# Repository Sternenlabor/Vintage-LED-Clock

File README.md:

# Vintage-LED-Clock
# WiFi configuration
SSID and credentials are kept in a separate file which is not included in GIT repository.   
Create file *credentials.h* in *src* folder and add SSID and WiFi password.   
e.g.:

    #ifndef _CREDENTIALS_H_
    #define _CREDENTIALS_H_

    const char cstrSSID[] = "MyNetwork";
    const char cstrPWD[] = "secret";

    #endif /* _CREDENTIALS_H_ */

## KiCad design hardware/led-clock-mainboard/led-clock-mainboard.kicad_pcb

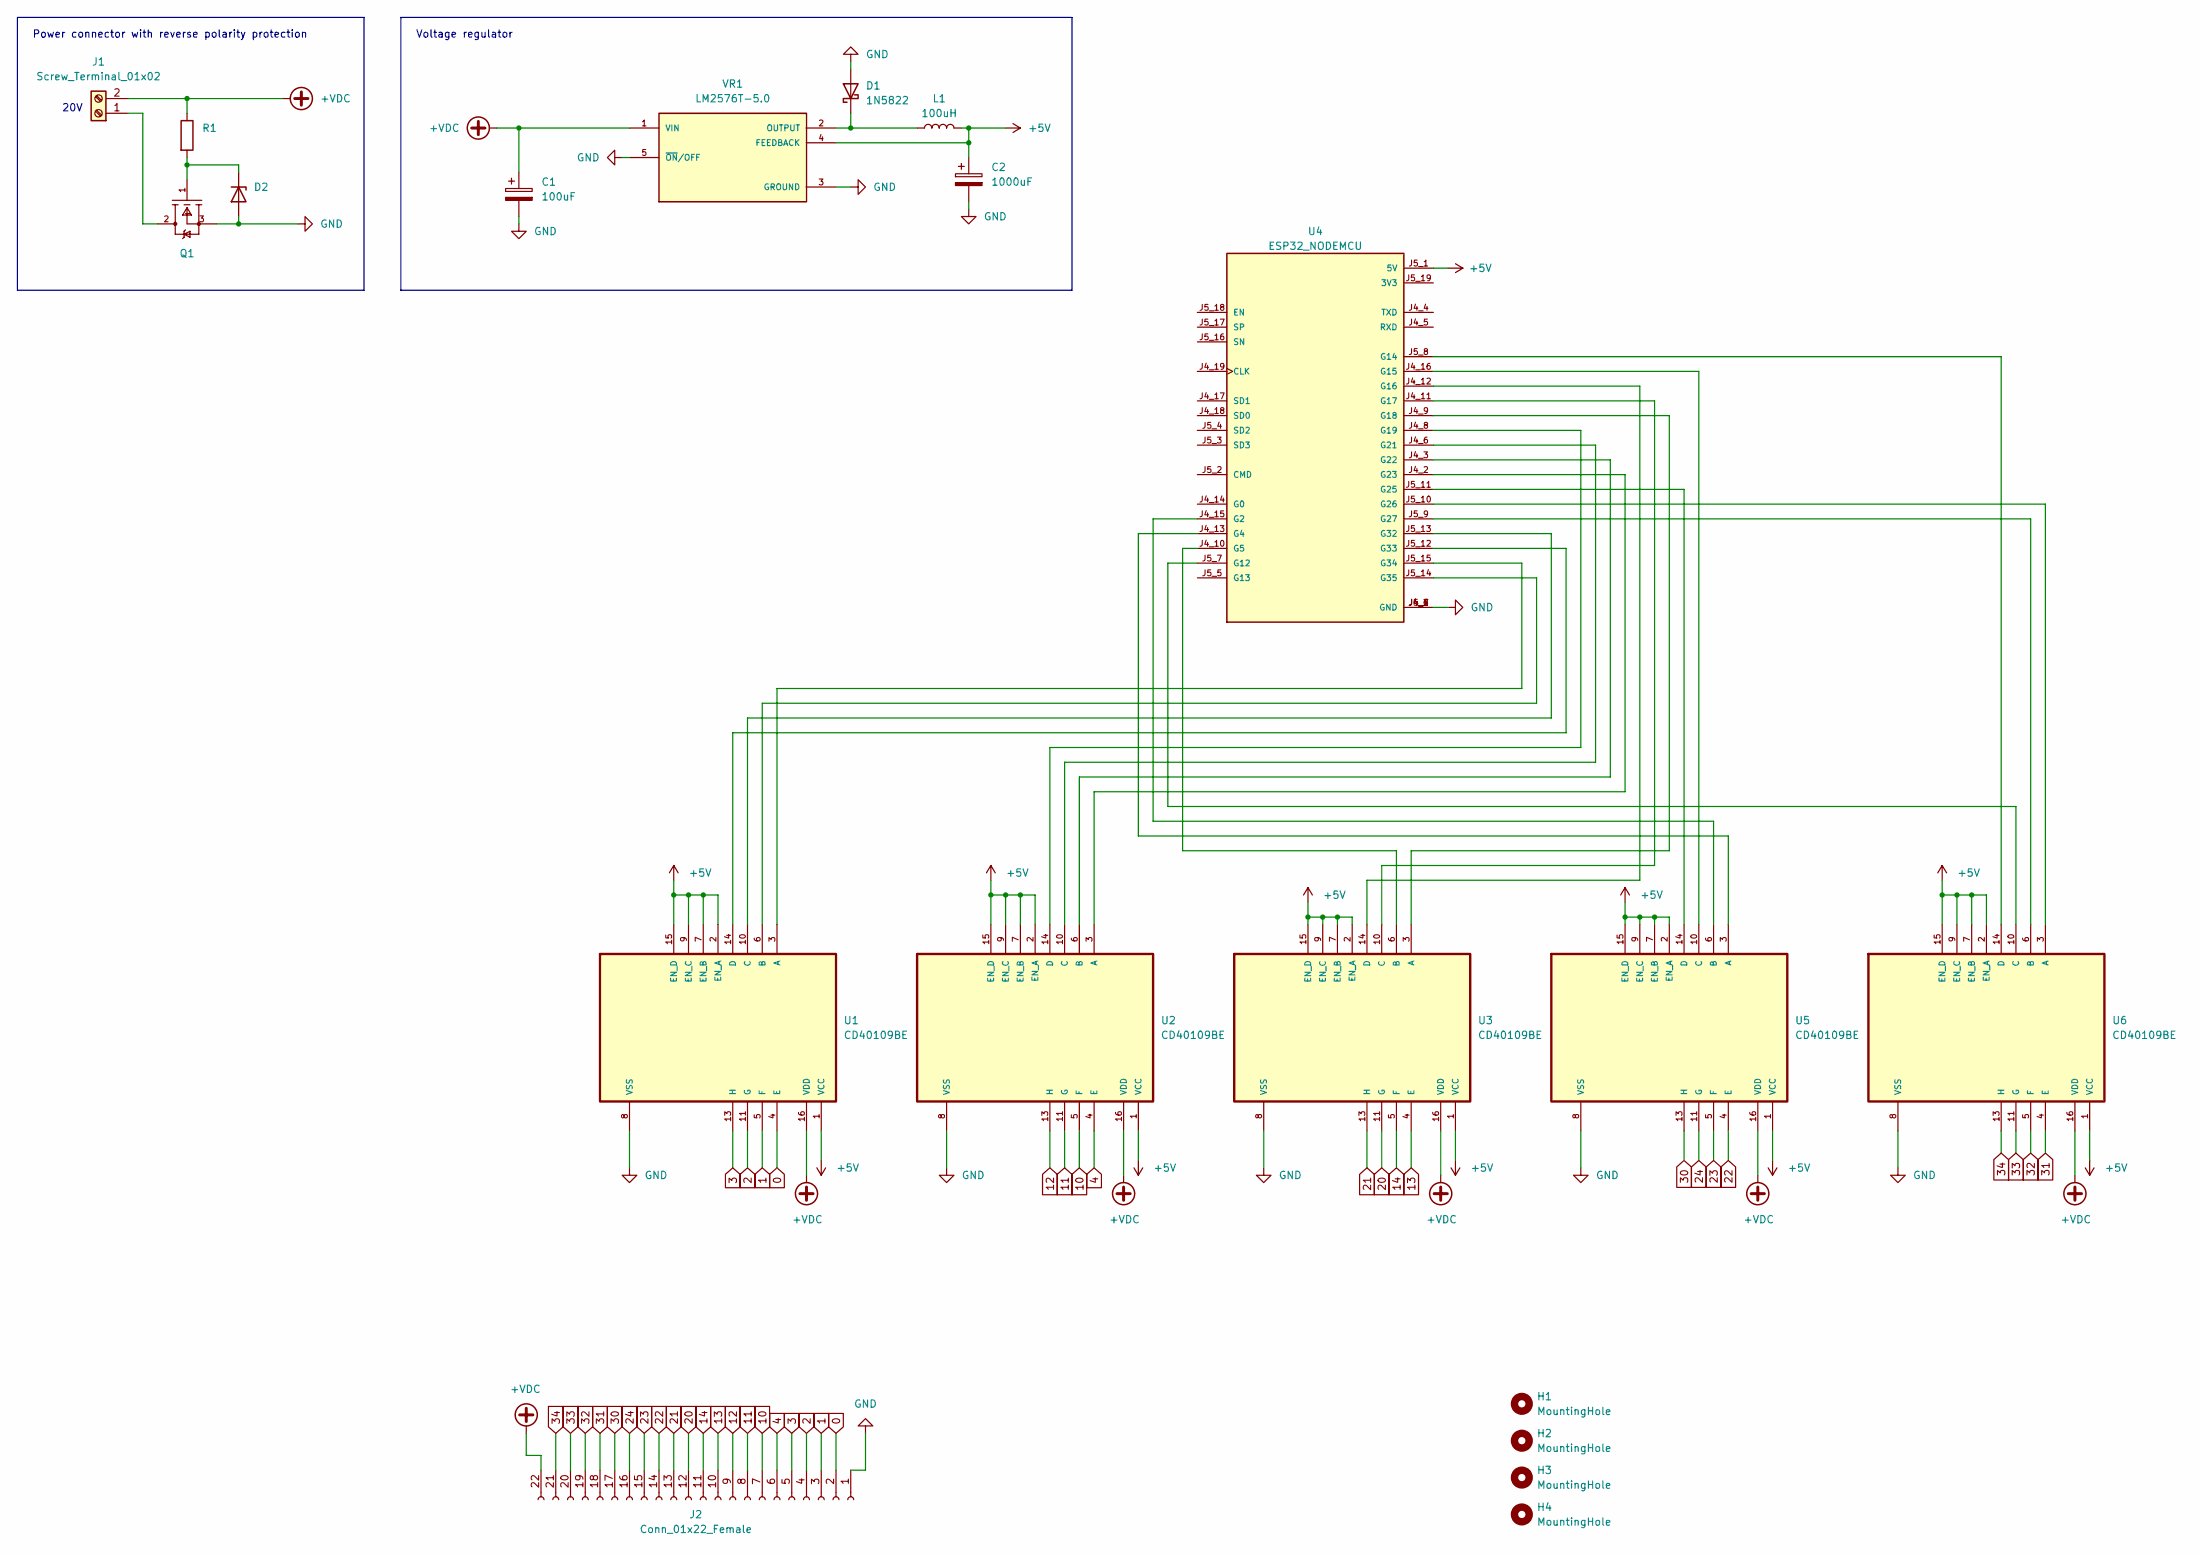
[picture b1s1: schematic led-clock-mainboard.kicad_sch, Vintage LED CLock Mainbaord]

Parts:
C1: 100uF; CP_Radial_D5.0mm_P2.50mm
C2: 1000uF; CP_Radial_D10.0mm_P5.00mm
D1: 1N5822; D_DO-201AD_P15.24mm_Horizontal
D2: (no value)
H1, H2, H3, H4: MountingHole; MountingHole_3.2mm_M3
J1: Screw_Terminal_01x02; TerminalBlock_Altech_AK300-2_P5.00mm
J2: Conn_01x22_Female; PinSocket_1x22_P2.54mm_Vertical
L1: 100uH; L_Radial_D9.5mm_P5.00mm_Fastron_07HVP
Q1: mouser part number 942-IRF1404PBF; digikey description MOSFET N-CH 40V 202A TO-220AB
R1: (no value)
U1, U2, U3, U5, U6: CD40109BE; DIP794W45P254L1969H508Q16
U4: ESP32_NODEMCU
VR1: LM2576T-5.0; TO170P1067X483X1651-5; PARTREV E

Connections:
0: J2.2, U1.4 (E)
1: J2.3, U1.5 (F)
2: J2.4, U1.11 (G)
3: J2.5, U1.13 (H)
4: J2.6, U2.4 (E)
10: J2.7, U2.5 (F)
11: J2.8, U2.11 (G)
12: J2.9, U2.13 (H)
13: J2.10, U3.4 (E)
14: J2.11, U3.5 (F)
20: J2.12, U3.11 (G)
21: J2.13, U3.13 (H)
22: J2.14, U5.4 (E)
23: J2.15, U5.5 (F)
24: J2.16, U5.11 (G)
30: J2.17, U5.13 (H)
31: J2.18, U6.4 (E)
32: J2.19, U6.5 (F)
33: J2.20, U6.11 (G)
34: J2.21, U6.13 (H)
+5V: C2.1, L1.2, U1.1 (VCC), U1.2 (EN_A), U1.7 (EN_B), U1.9 (EN_C), U1.15 (EN_D), U2.1 (VCC), U2.2 (EN_A), U2.7 (EN_B), U2.9 (EN_C), U2.15 (EN_D), U3.1 (VCC), U3.2 (EN_A), U3.7 (EN_B), U3.9 (EN_C), U3.15 (EN_D), U4.J5_1 (5V), U5.1 (VCC), U5.2 (EN_A), U5.7 (EN_B), U5.9 (EN_C), U5.15 (EN_D), U6.1 (VCC), U6.2 (EN_A), U6.7 (EN_B), U6.9 (EN_C), U6.15 (EN_D), VR1.4 (FEEDBACK)
+VDC: C1.1, J1.2, J2.22, R1.1, U1.16 (VDD), U2.16 (VDD), U3.16 (VDD), U5.16 (VDD), U6.16 (VDD), VR1.1 (VIN)
GND: C1.2, C2.2, D1.2 (A), D2.2 (A), J2.1, Q1.3 (SOURCE), U1.8 (VSS), U2.8 (VSS), U3.8 (VSS), U4.J4_1 (GND), U4.J4_7 (GND), U4.J5_6 (GND), U5.8 (VSS), U6.8 (VSS), VR1.3 (GROUND), VR1.5 (~ON/OFF)
unnamed: D1.1 (K), L1.1, VR1.2 (OUTPUT)
unnamed: D2.1 (K), Q1.1 (GATE), R1.2
unnamed: J1.1, Q1.2 (DRAIN)
unnamed: U1.3 (A), U4.J5_15 (G34)
unnamed: U1.6 (B), U4.J5_14 (G35)
unnamed: U1.10 (C), U4.J5_13 (G32)
unnamed: U1.14 (D), U4.J5_12 (G33)
unnamed: U2.3 (A), U4.J4_2 (G23)
unnamed: U2.6 (B), U4.J4_3 (G22)
unnamed: U2.10 (C), U4.J4_6 (G21)
unnamed: U2.14 (D), U4.J4_8 (G19)
unnamed: U3.3 (A), U4.J4_9 (G18)
unnamed: U3.6 (B), U4.J4_10 (G5)
unnamed: U3.10 (C), U4.J4_11 (G17)
unnamed: U3.14 (D), U4.J4_12 (G16)
unnamed: U4.J4_13 (G4), U5.3 (A)
unnamed: U4.J4_15 (G2), U5.6 (B)
unnamed: U4.J4_16 (G15), U5.10 (C)
unnamed: U4.J5_7 (G12), U6.10 (C)
unnamed: U4.J5_8 (G14), U6.14 (D)
unnamed: U4.J5_9 (G27), U6.6 (B)
unnamed: U4.J5_10 (G26), U6.3 (A)
unnamed: U4.J5_11 (G25), U5.14 (D)

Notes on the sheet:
20V
Power connector with reverse polarity protection
Voltage regulator

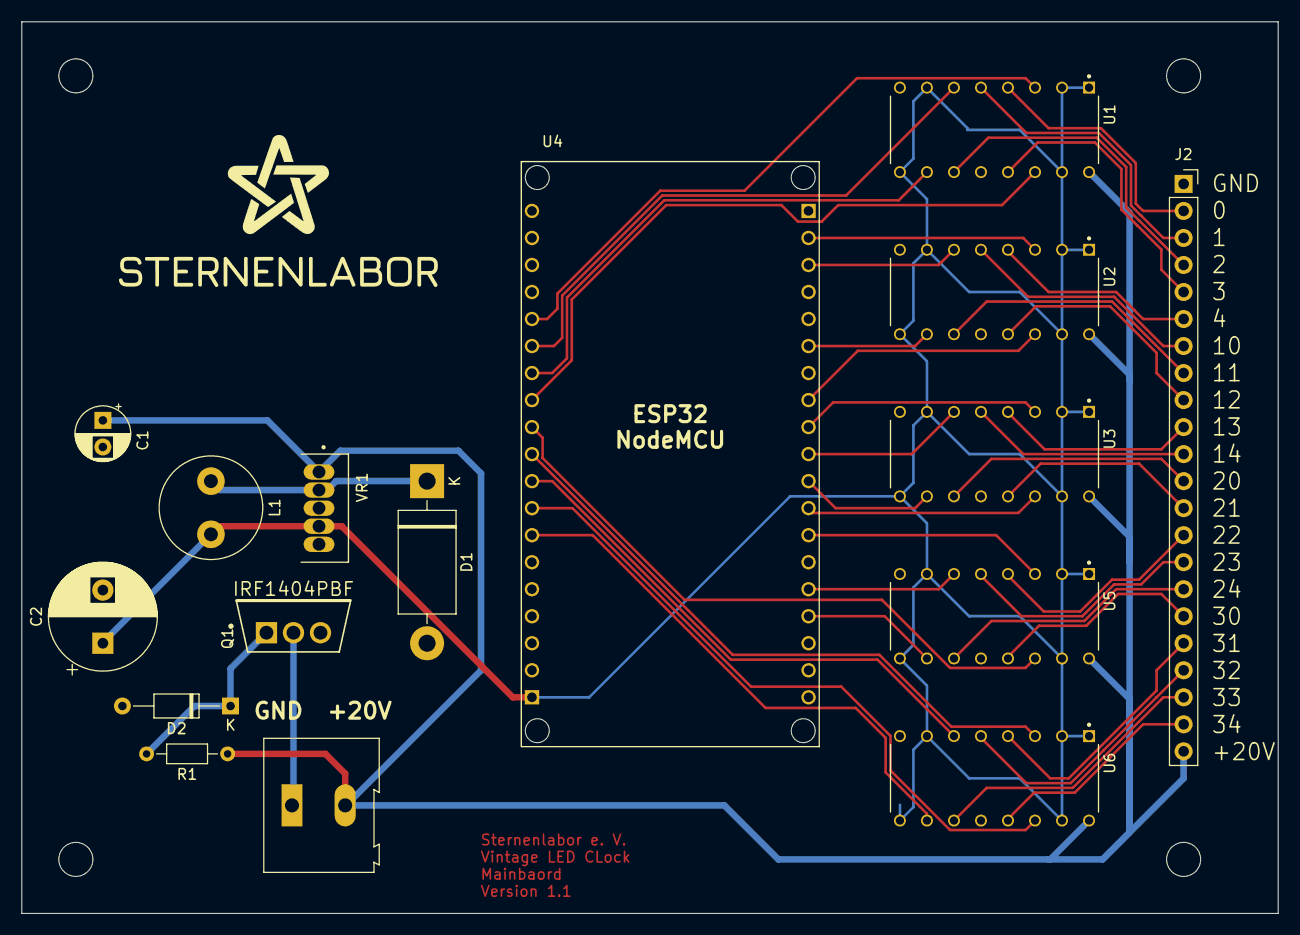
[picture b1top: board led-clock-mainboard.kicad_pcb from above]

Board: 2 copper layers, 118.1 x 83.8 mm, 20 parts (0 on the bottom side), 46 nets.

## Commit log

2022-09-15 initial release
2022-09-15 do not track
2023-04-11 Moved wifi credentials to external file.
2023-04-11 Just cosmetics - should work as before (test it)
2023-04-11 Added dimming (needs testing)
2023-04-11 Use separate PWM for each digit (never work :) )
2023-04-13 Changed brigtness and clock off on startup
2023-04-15 Fixed a PCB layout issue (missing track) and added reverse power protection
2023-04-15 move README and LICENSE back to root
2023-04-15 added LED case design
2023-04-15 small modification for LED case
2023-05-09 Added Tasker
